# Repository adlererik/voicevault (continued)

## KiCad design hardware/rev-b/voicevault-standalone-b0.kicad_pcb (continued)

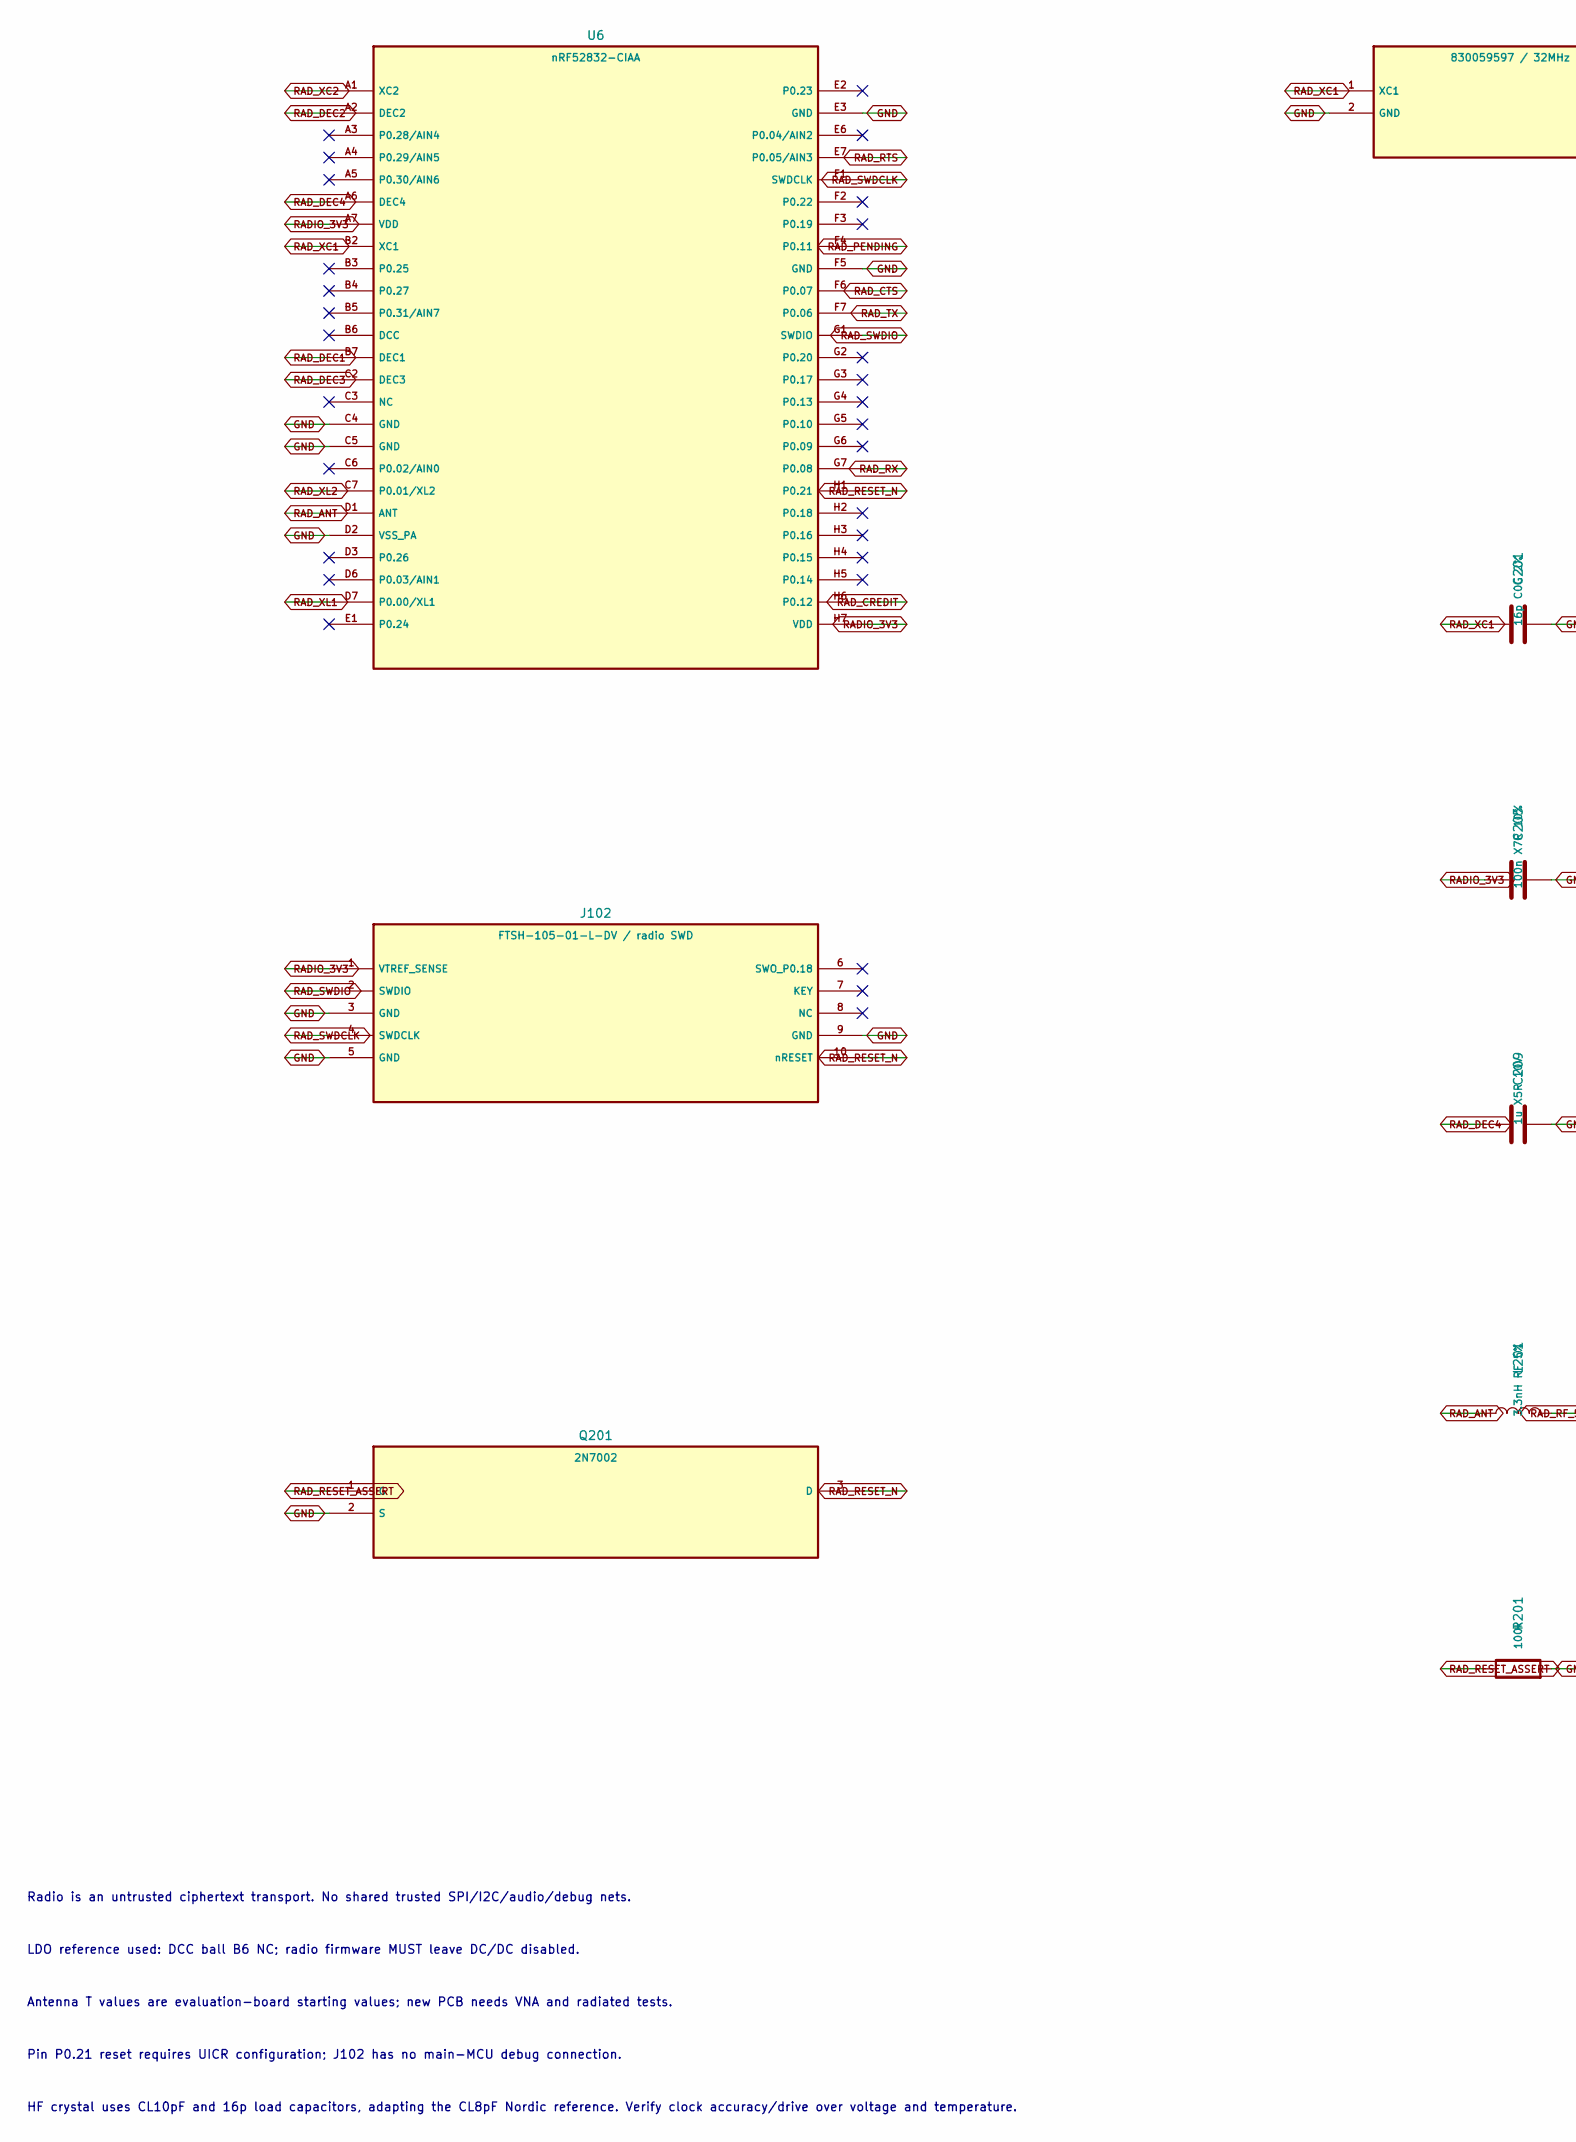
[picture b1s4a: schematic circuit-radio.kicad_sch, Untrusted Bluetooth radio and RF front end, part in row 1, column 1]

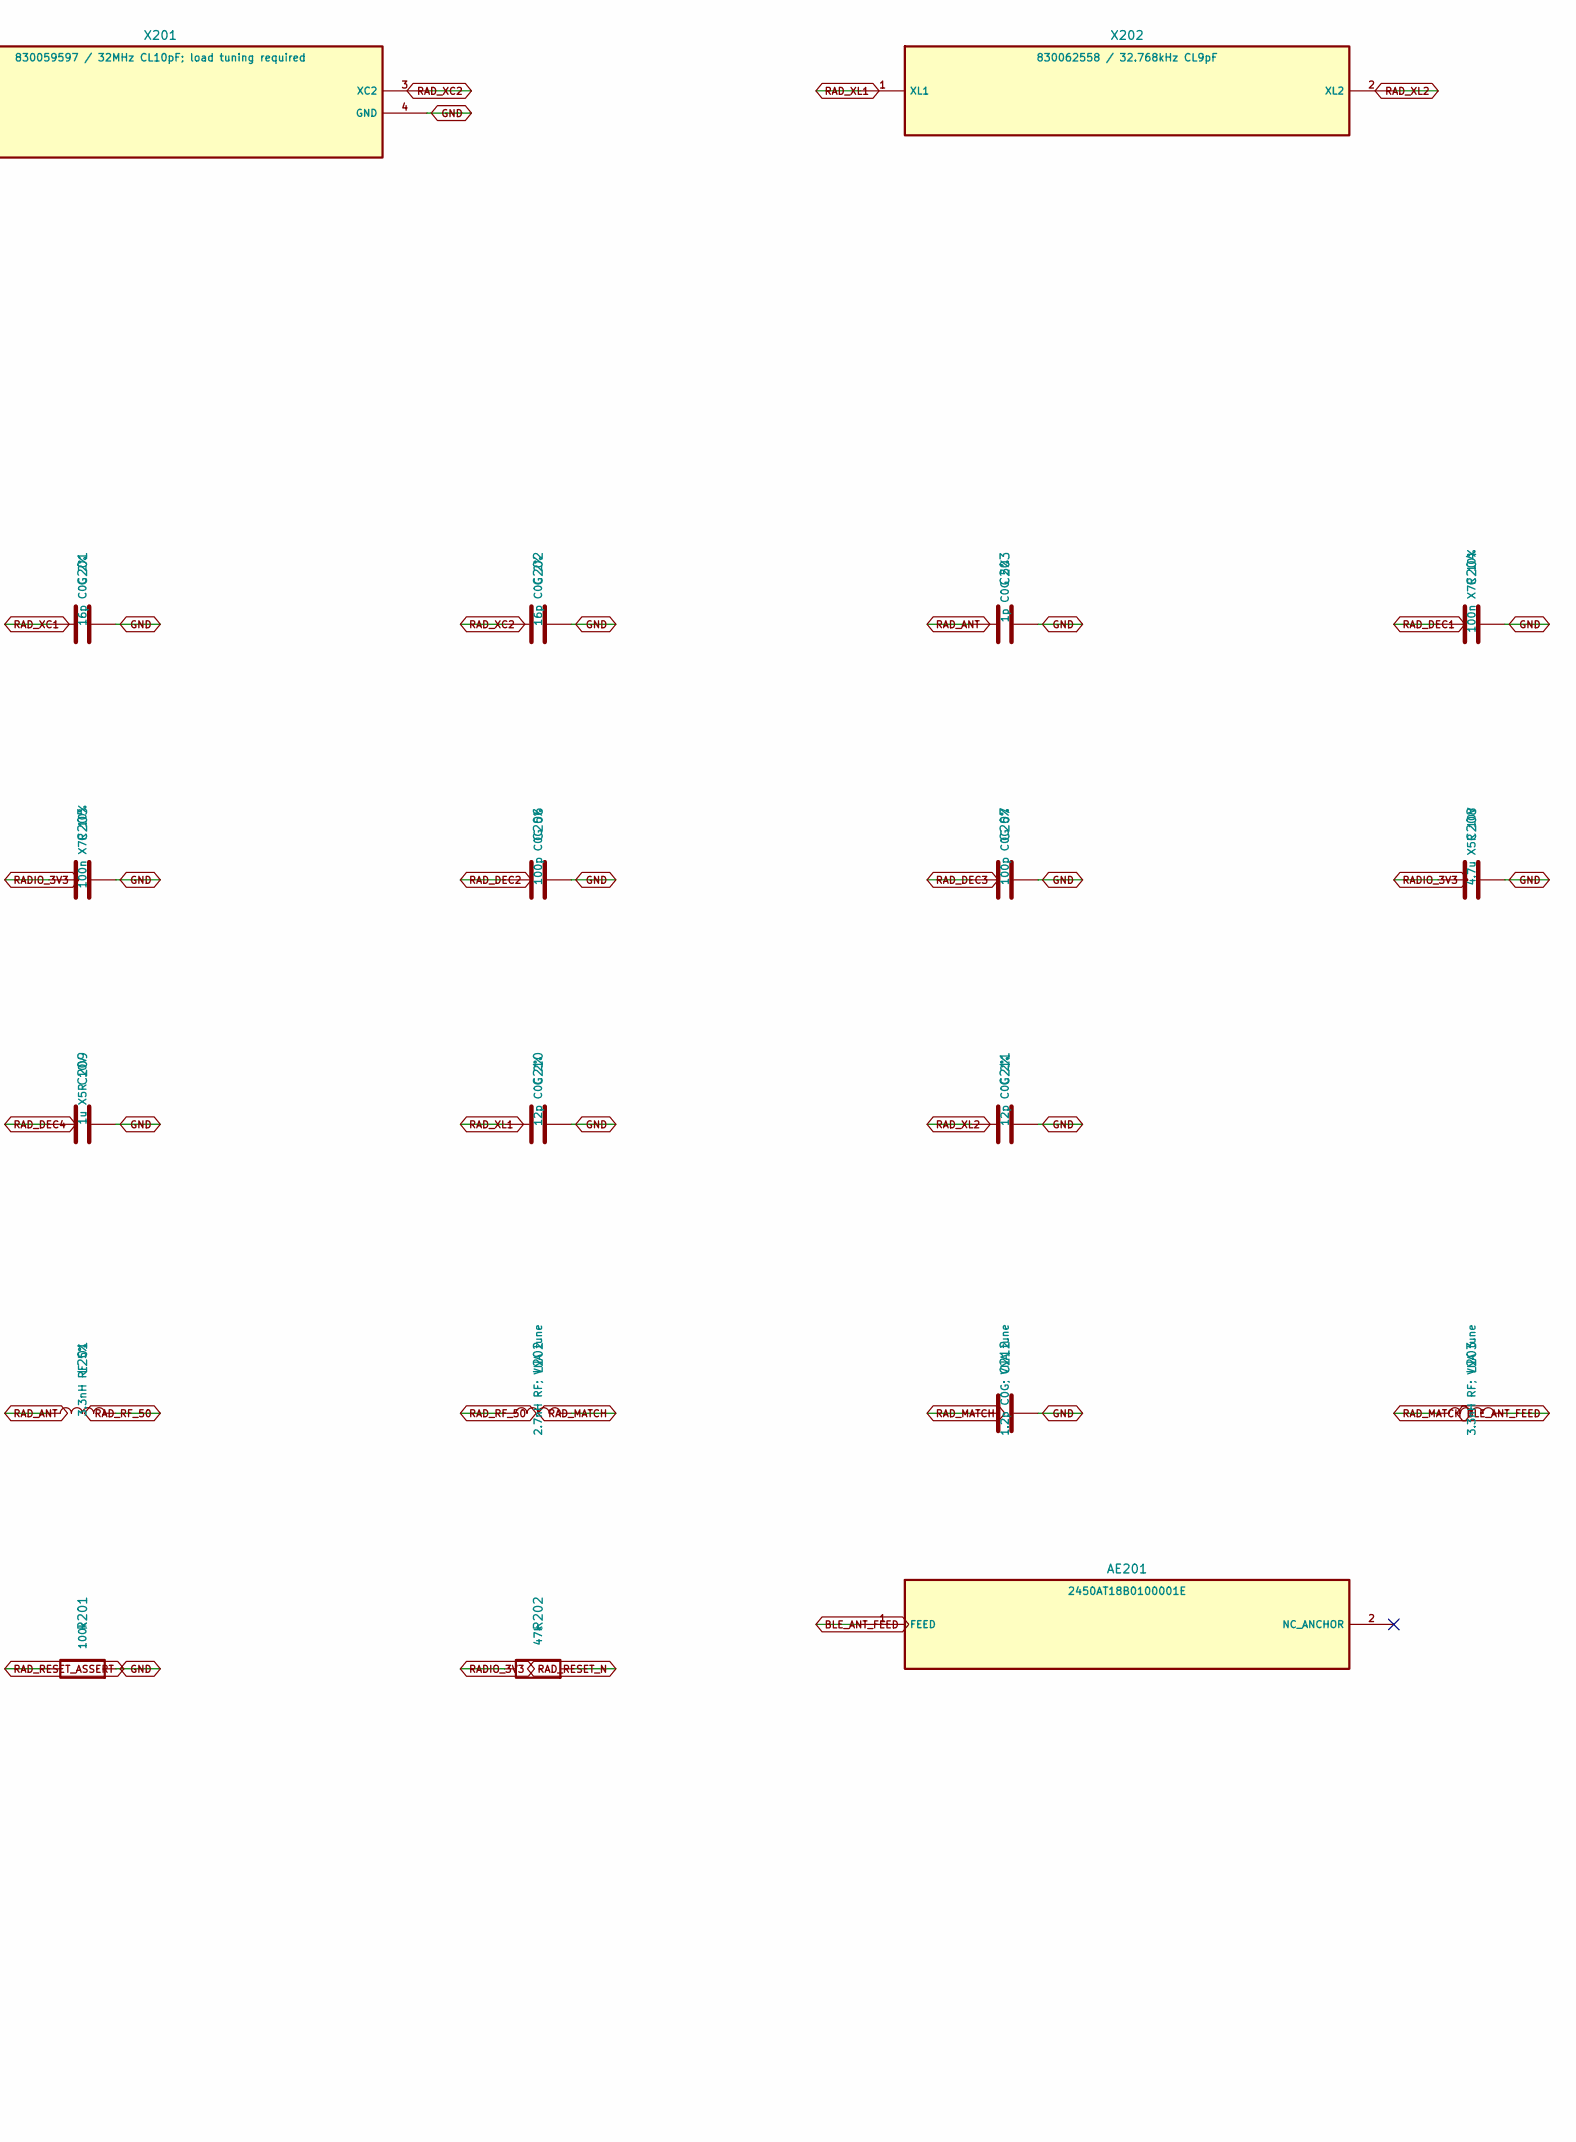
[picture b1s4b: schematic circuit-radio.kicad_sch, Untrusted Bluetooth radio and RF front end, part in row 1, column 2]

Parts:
AE201: 2450AT18B0100001E; Johanson_2450AT18x100
C201, C202: 16p C0G 2%; C_0201_0603Metric
C203: 1p C0G 5%; C_0201_0603Metric
C204, C205: 100n X7R 10%; C_0201_0603Metric
C206, C207: 100p C0G 5%; C_0201_0603Metric
C208: 4.7u X5R 10V; C_0603_1608Metric
C209: 1u X5R 10V; C_0402_1005Metric
C210, C211: 12p C0G 2%; C_0201_0603Metric
C212: 1.2p C0G; VNA tune; C_0402_1005Metric
J102: FTSH-105-01-L-DV / radio SWD; Samtec_FTSH-105-01-L-DV
L201: 3.3nH RF 5%; L_0201_0603Metric
L202: 2.7nH RF; VNA tune; L_0402_1005Metric
L203: 3.3nH RF; VNA tune; L_0402_1005Metric
Q201: 2N7002; SOT-23
R201: 100k; R_0402_1005Metric
R202: 47k; R_0402_1005Metric
U6: nRF52832-CIAA; nRF52832_CIAA_Nordic
X201: 830059597 / 32MHz CL10pF; load tuning required; Crystal_SMD_2016-4Pin_2.0x1.6mm
X202: 830062558 / 32.768kHz CL9pF; Crystal_SMD_2012-2Pin_2.0x1.2mm

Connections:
BLE_ANT_FEED: AE201.1 (FEED), L203.2
GND: C201.2, C202.2, C203.2, C204.2, C205.2, C206.2, C207.2, C208.2, C209.2, C210.2, C211.2, C212.2, J102.3 (GND), J102.5 (GND), J102.9 (GND), Q201.2 (S), R201.2, U6.C4 (GND), U6.C5 (GND), U6.D2 (VSS_PA), U6.E3 (GND), U6.F5 (GND), X201.2 (GND), X201.4 (GND); also elsewhere on the board
RADIO_3V3: C205.1, C208.1, J102.1 (VTREF_SENSE), R202.1, U6.A7 (VDD), U6.H7 (VDD); also elsewhere on the board
RAD_ANT: C203.1, L201.1, U6.D1 (ANT)
RAD_CREDIT: U6.H6 (P0.12); also elsewhere on the board
RAD_CTS: U6.F6 (P0.07); also elsewhere on the board
RAD_DEC1: C204.1, U6.B7 (DEC1)
RAD_DEC2: C206.1, U6.A2 (DEC2)
RAD_DEC3: C207.1, U6.C2 (DEC3)
RAD_DEC4: C209.1, U6.A6 (DEC4)
RAD_MATCH: C212.1, L202.2, L203.1
RAD_PENDING: U6.F4 (P0.11); also elsewhere on the board
RAD_RESET_ASSERT: Q201.1 (G), R201.1; also elsewhere on the board
RAD_RESET_N: J102.10 (nRESET), Q201.3 (D), R202.2, U6.H1 (P0.21)
RAD_RF_50: L201.2, L202.1
RAD_RTS: U6.E7 (P0.05/AIN3); also elsewhere on the board
RAD_RX: U6.G7 (P0.08); also elsewhere on the board
RAD_SWDCLK: J102.4 (SWDCLK), U6.F1 (SWDCLK)
RAD_SWDIO: J102.2 (SWDIO), U6.G1 (SWDIO)
RAD_TX: U6.F7 (P0.06); also elsewhere on the board
RAD_XC1: C201.1, U6.B2 (XC1), X201.1 (XC1)
RAD_XC2: C202.1, U6.A1 (XC2), X201.3 (XC2)
RAD_XL1: C210.1, U6.D7 (P0.00/XL1), X202.1 (XL1)
RAD_XL2: C211.1, U6.C7 (P0.01/XL2), X202.2 (XL2)

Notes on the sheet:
Radio is an untrusted ciphertext transport. No shared trusted SPI/I2C/audio/debug nets.
LDO reference used: DCC ball B6 NC; radio firmware MUST leave DC/DC disabled.
Antenna T values are evaluation-board starting values; new PCB needs VNA and radiated tests.
Pin P0.21 reset requires UICR configuration; J102 has no main-MCU debug connection.
HF crystal uses CL10pF and 16p load capacitors, adapting the CL8pF Nordic reference. Verify clock accuracy/drive over voltage and temperature.

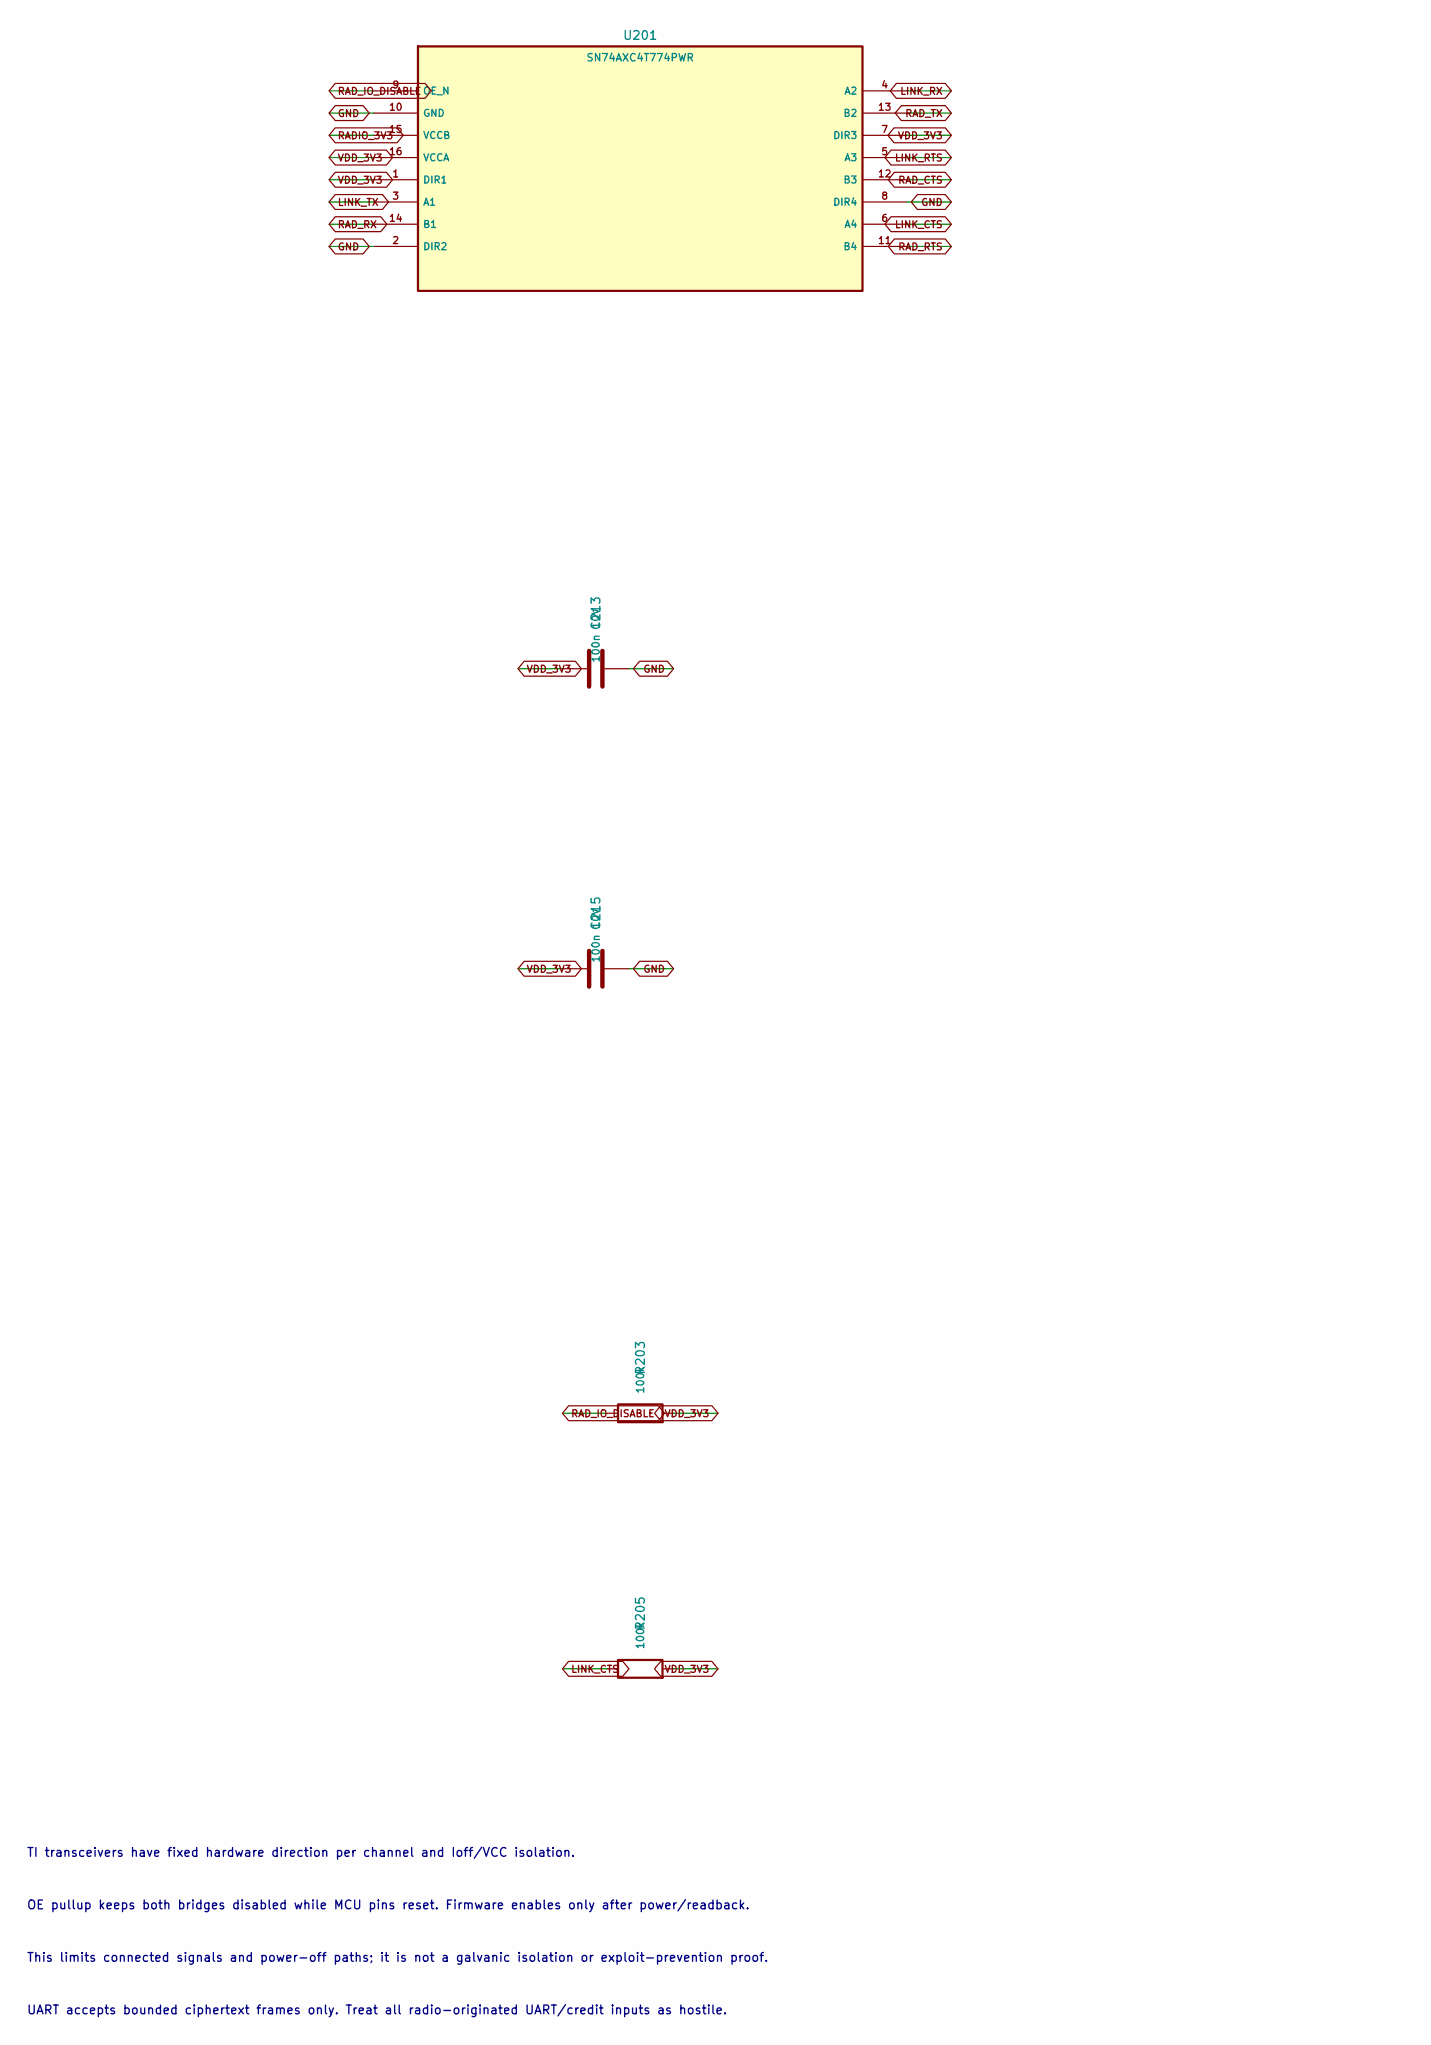
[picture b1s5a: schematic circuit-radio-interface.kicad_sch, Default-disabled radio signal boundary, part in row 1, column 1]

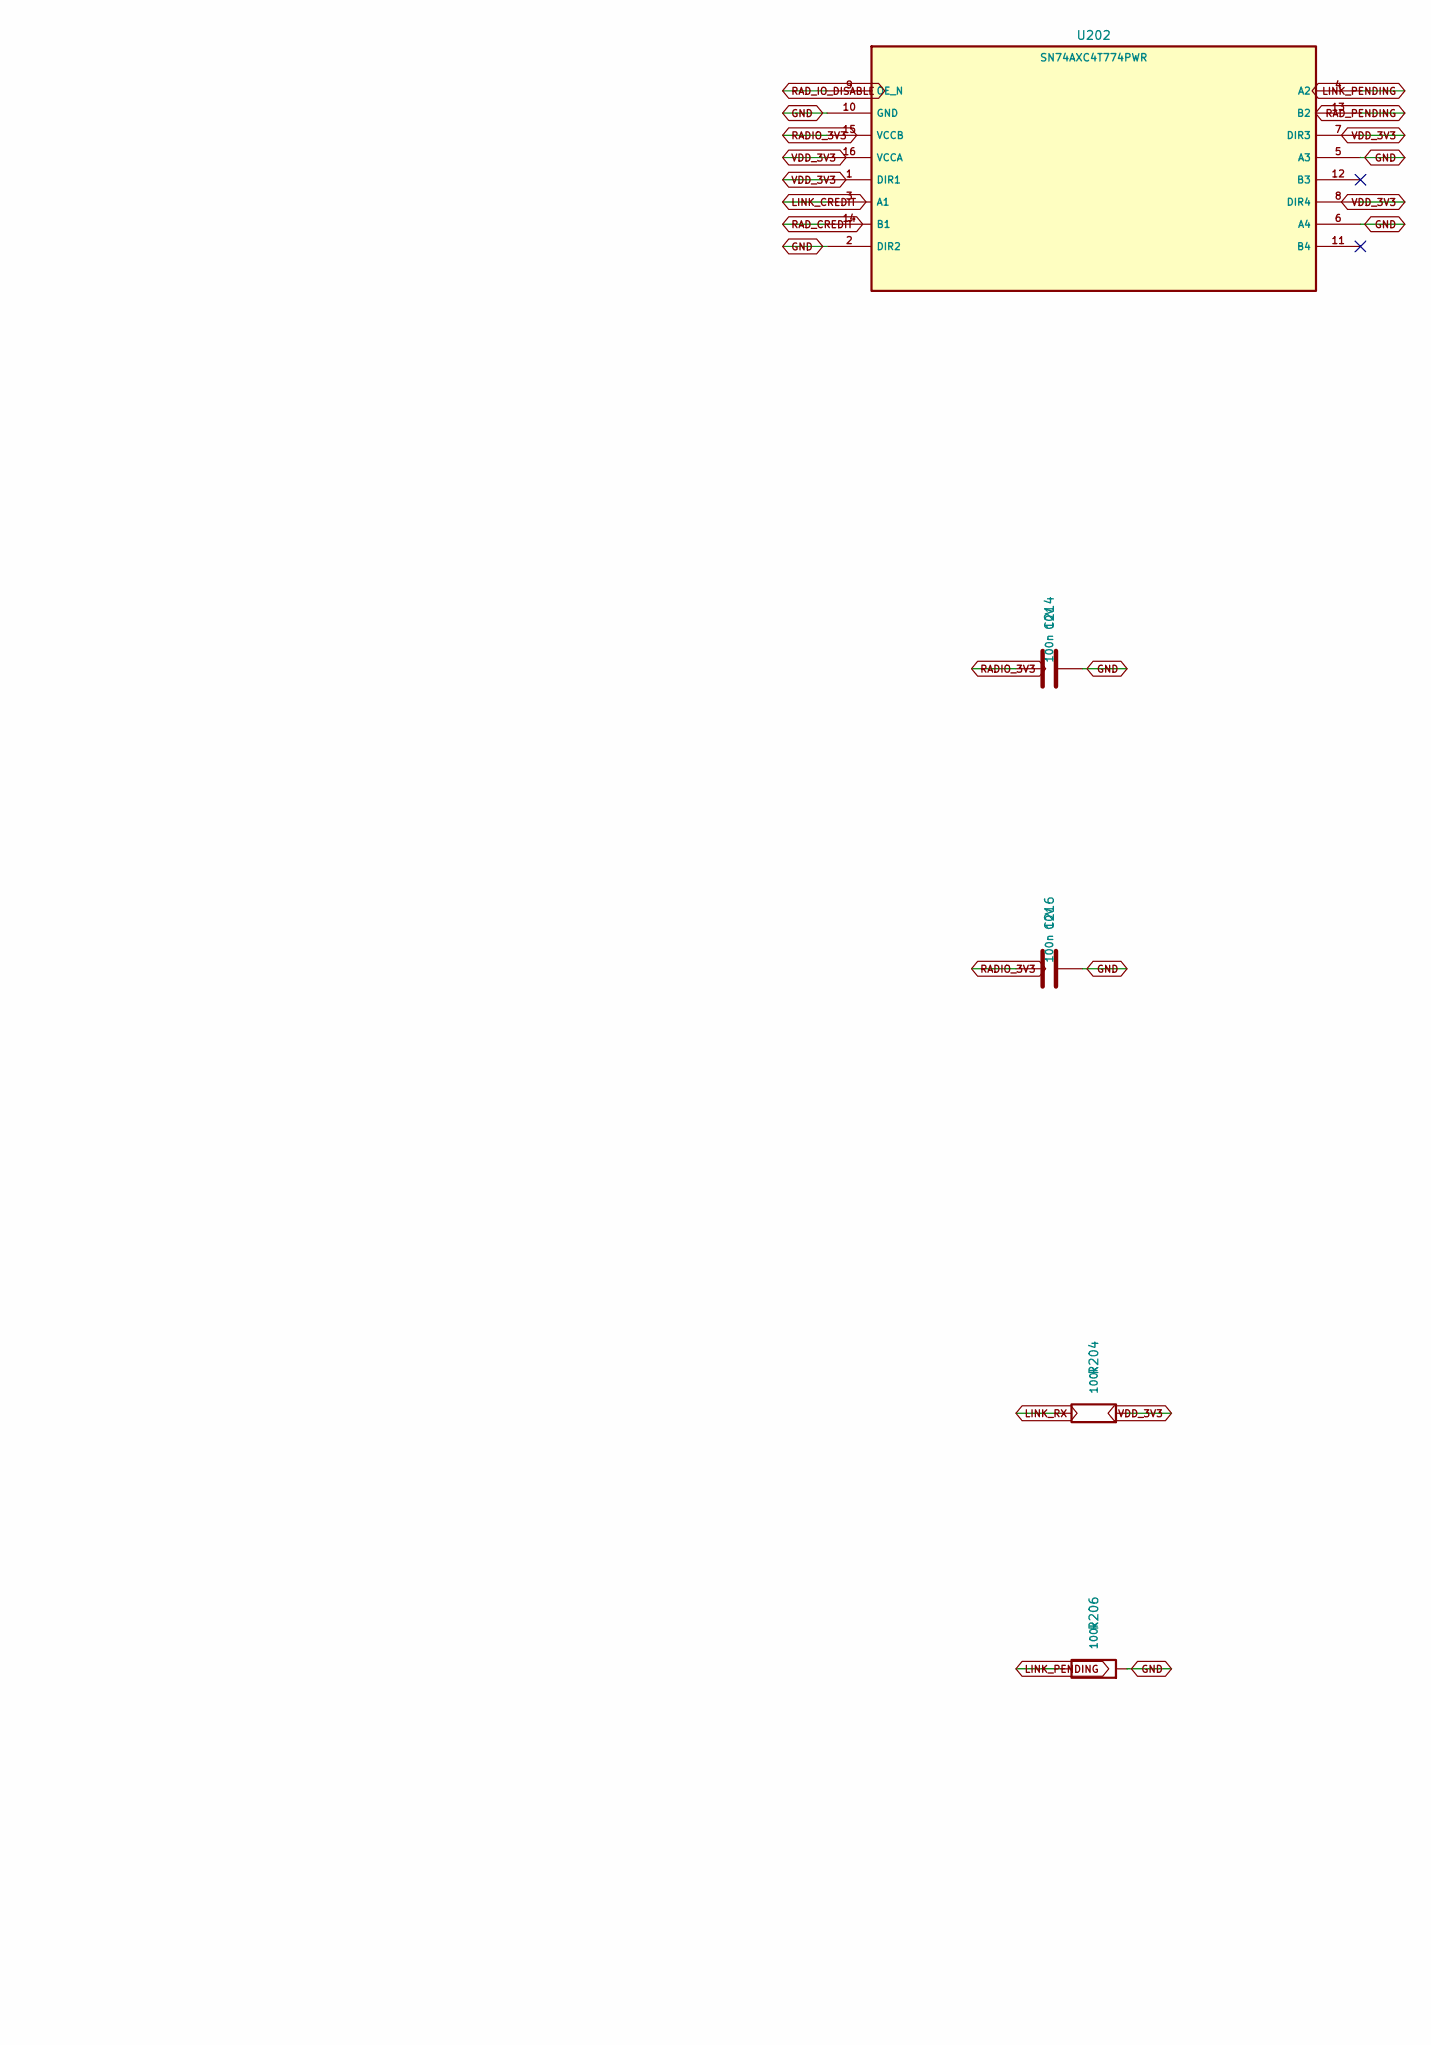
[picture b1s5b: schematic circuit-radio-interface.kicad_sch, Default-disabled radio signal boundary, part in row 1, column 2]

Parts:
C213, C214, C215, C216: 100n 10V; C_0402_1005Metric
R203, R204, R205, R206: 100k; R_0402_1005Metric
U201, U202: SN74AXC4T774PWR; TSSOP-16_4.4x5mm_P0.65mm

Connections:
GND: C213.2, C214.2, C215.2, C216.2, R206.2, U201.2 (DIR2), U201.8 (DIR4), U201.10 (GND), U202.2 (DIR2), U202.5 (A3), U202.6 (A4), U202.10 (GND); also elsewhere on the board
LINK_CREDIT: U202.3 (A1); also elsewhere on the board
LINK_CTS: R205.1, U201.6 (A4); also elsewhere on the board
LINK_PENDING: R206.1, U202.4 (A2); also elsewhere on the board
LINK_RTS: U201.5 (A3); also elsewhere on the board
LINK_RX: R204.1, U201.4 (A2); also elsewhere on the board
LINK_TX: U201.3 (A1); also elsewhere on the board
RADIO_3V3: C214.1, C216.1, U201.15 (VCCB), U202.15 (VCCB); also elsewhere on the board
RAD_CREDIT: U202.14 (B1); also elsewhere on the board
RAD_CTS: U201.12 (B3); also elsewhere on the board
RAD_IO_DISABLE: R203.1, U201.9 (OE_N), U202.9 (OE_N); also elsewhere on the board
RAD_PENDING: U202.13 (B2); also elsewhere on the board
RAD_RTS: U201.11 (B4); also elsewhere on the board
RAD_RX: U201.14 (B1); also elsewhere on the board
RAD_TX: U201.13 (B2); also elsewhere on the board
VDD_3V3: C213.1, C215.1, R203.2, R204.2, R205.2, U201.1 (DIR1), U201.7 (DIR3), U201.16 (VCCA), U202.1 (DIR1), U202.7 (DIR3), U202.8 (DIR4), U202.16 (VCCA); also elsewhere on the board

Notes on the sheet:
TI transceivers have fixed hardware direction per channel and Ioff/VCC isolation.
OE pullup keeps both bridges disabled while MCU pins reset. Firmware enables only after power/readback.
This limits connected signals and power-off paths; it is not a galvanic isolation or exploit-prevention proof.
UART accepts bounded ciphertext frames only. Treat all radio-originated UART/credit inputs as hostile.

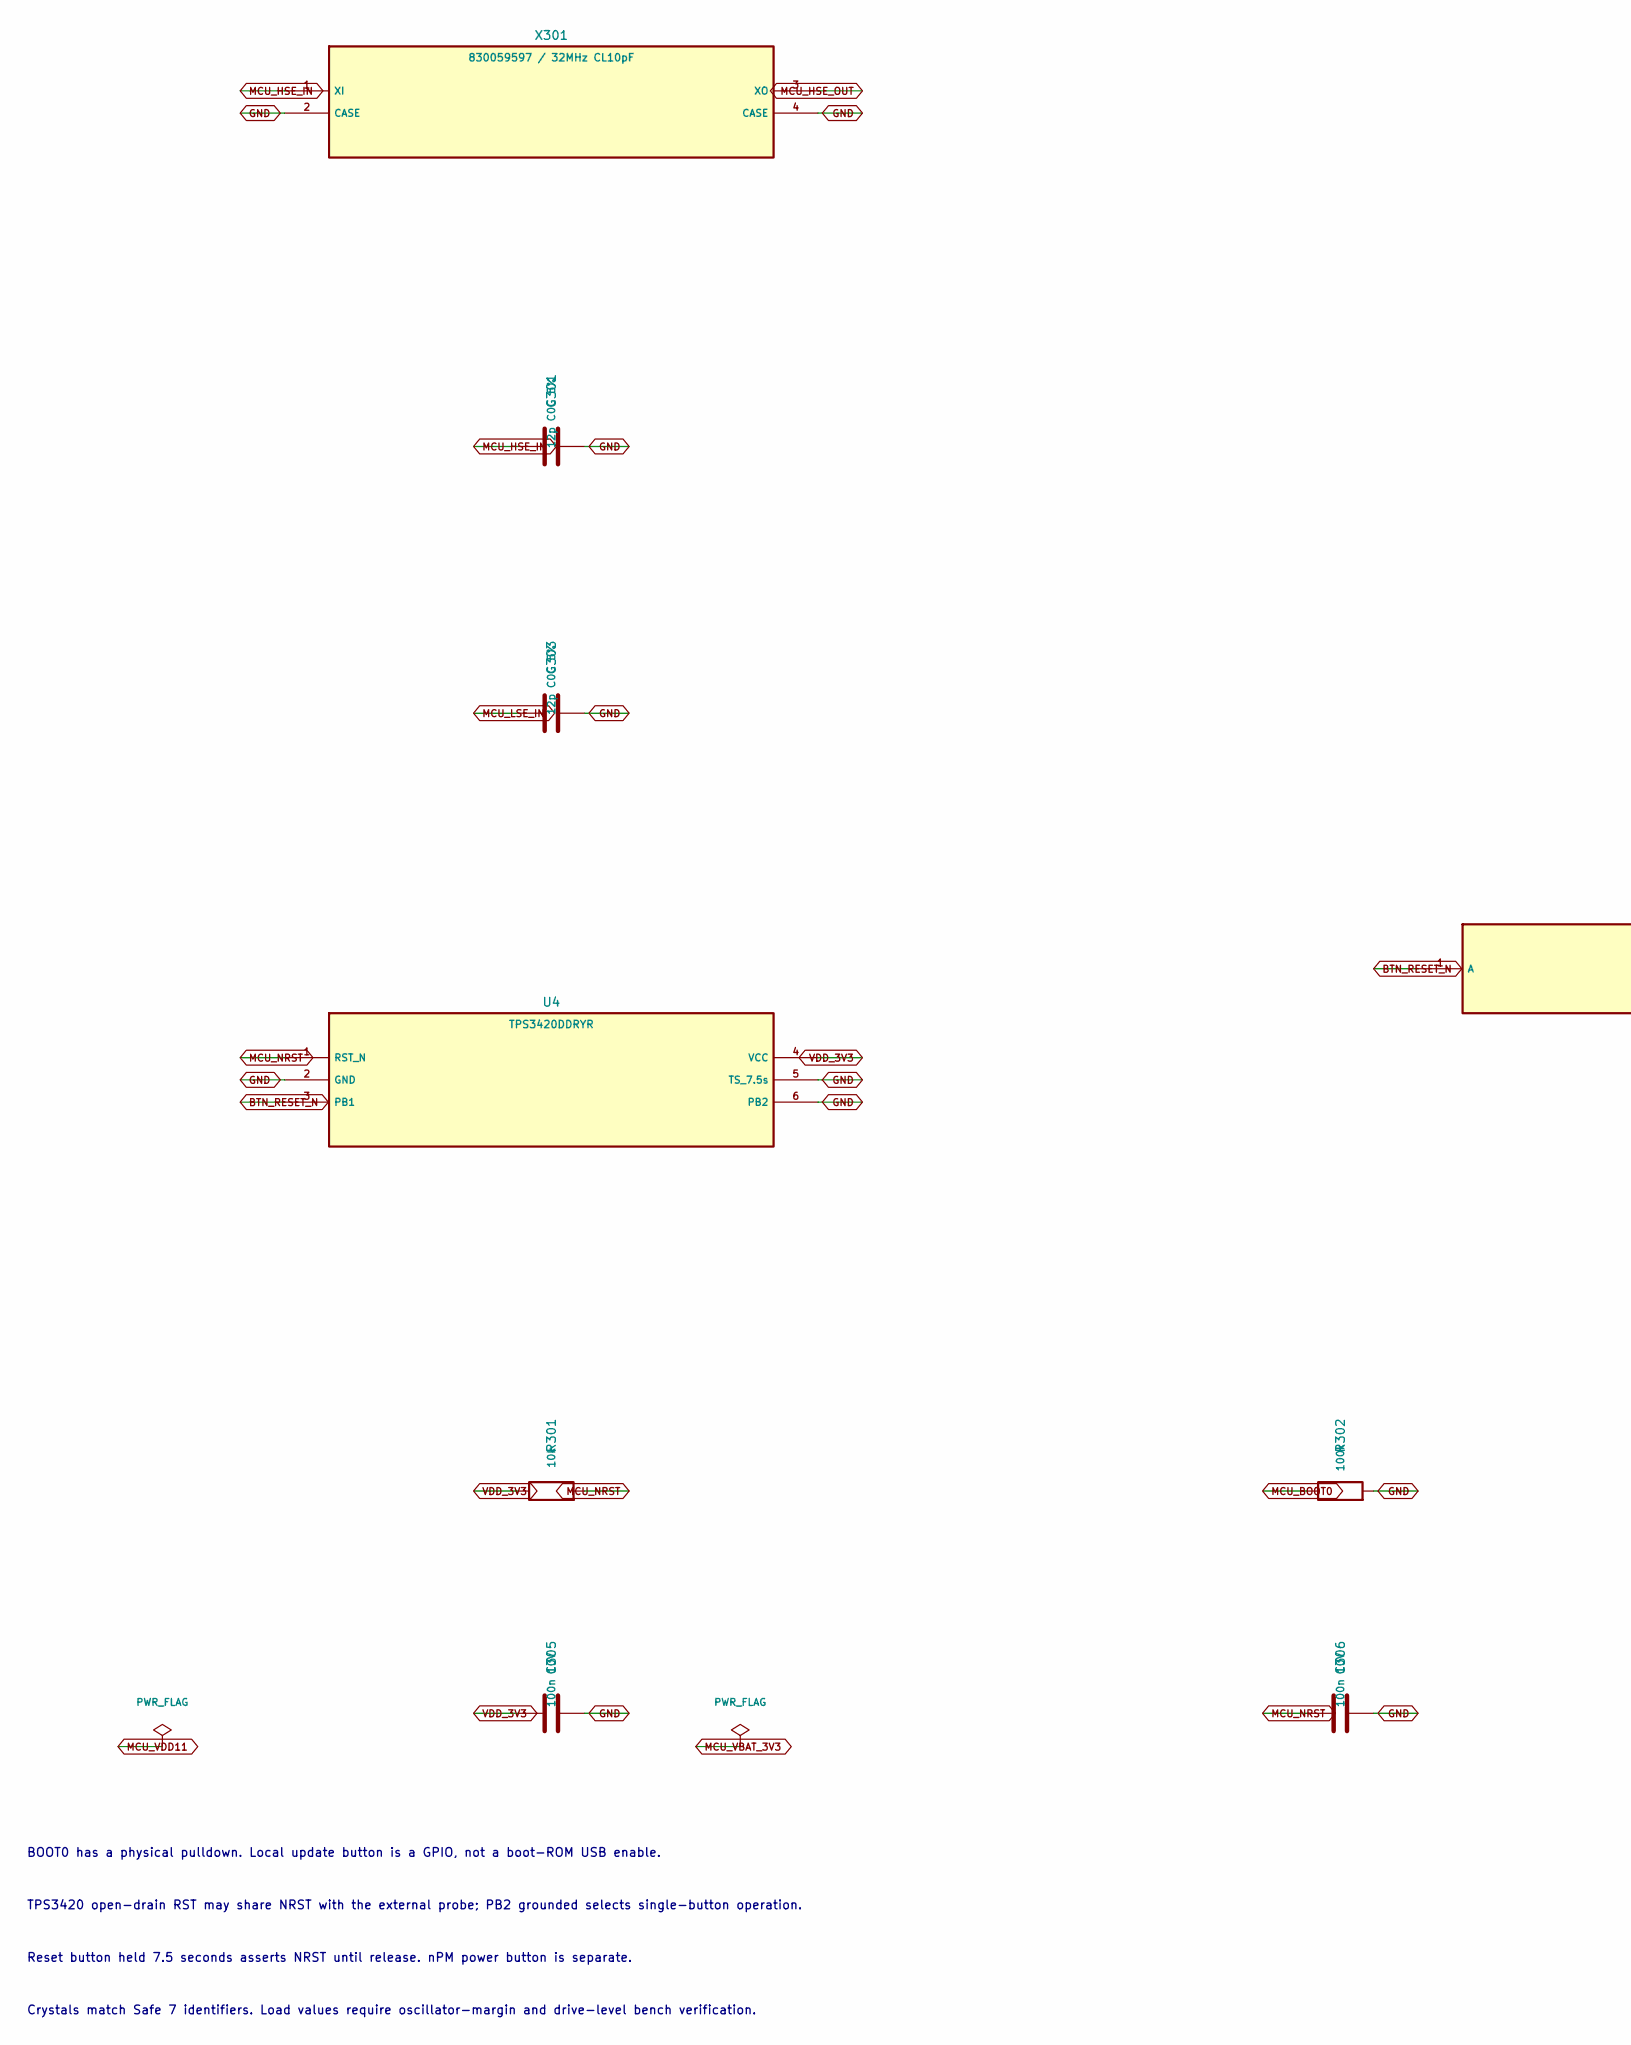
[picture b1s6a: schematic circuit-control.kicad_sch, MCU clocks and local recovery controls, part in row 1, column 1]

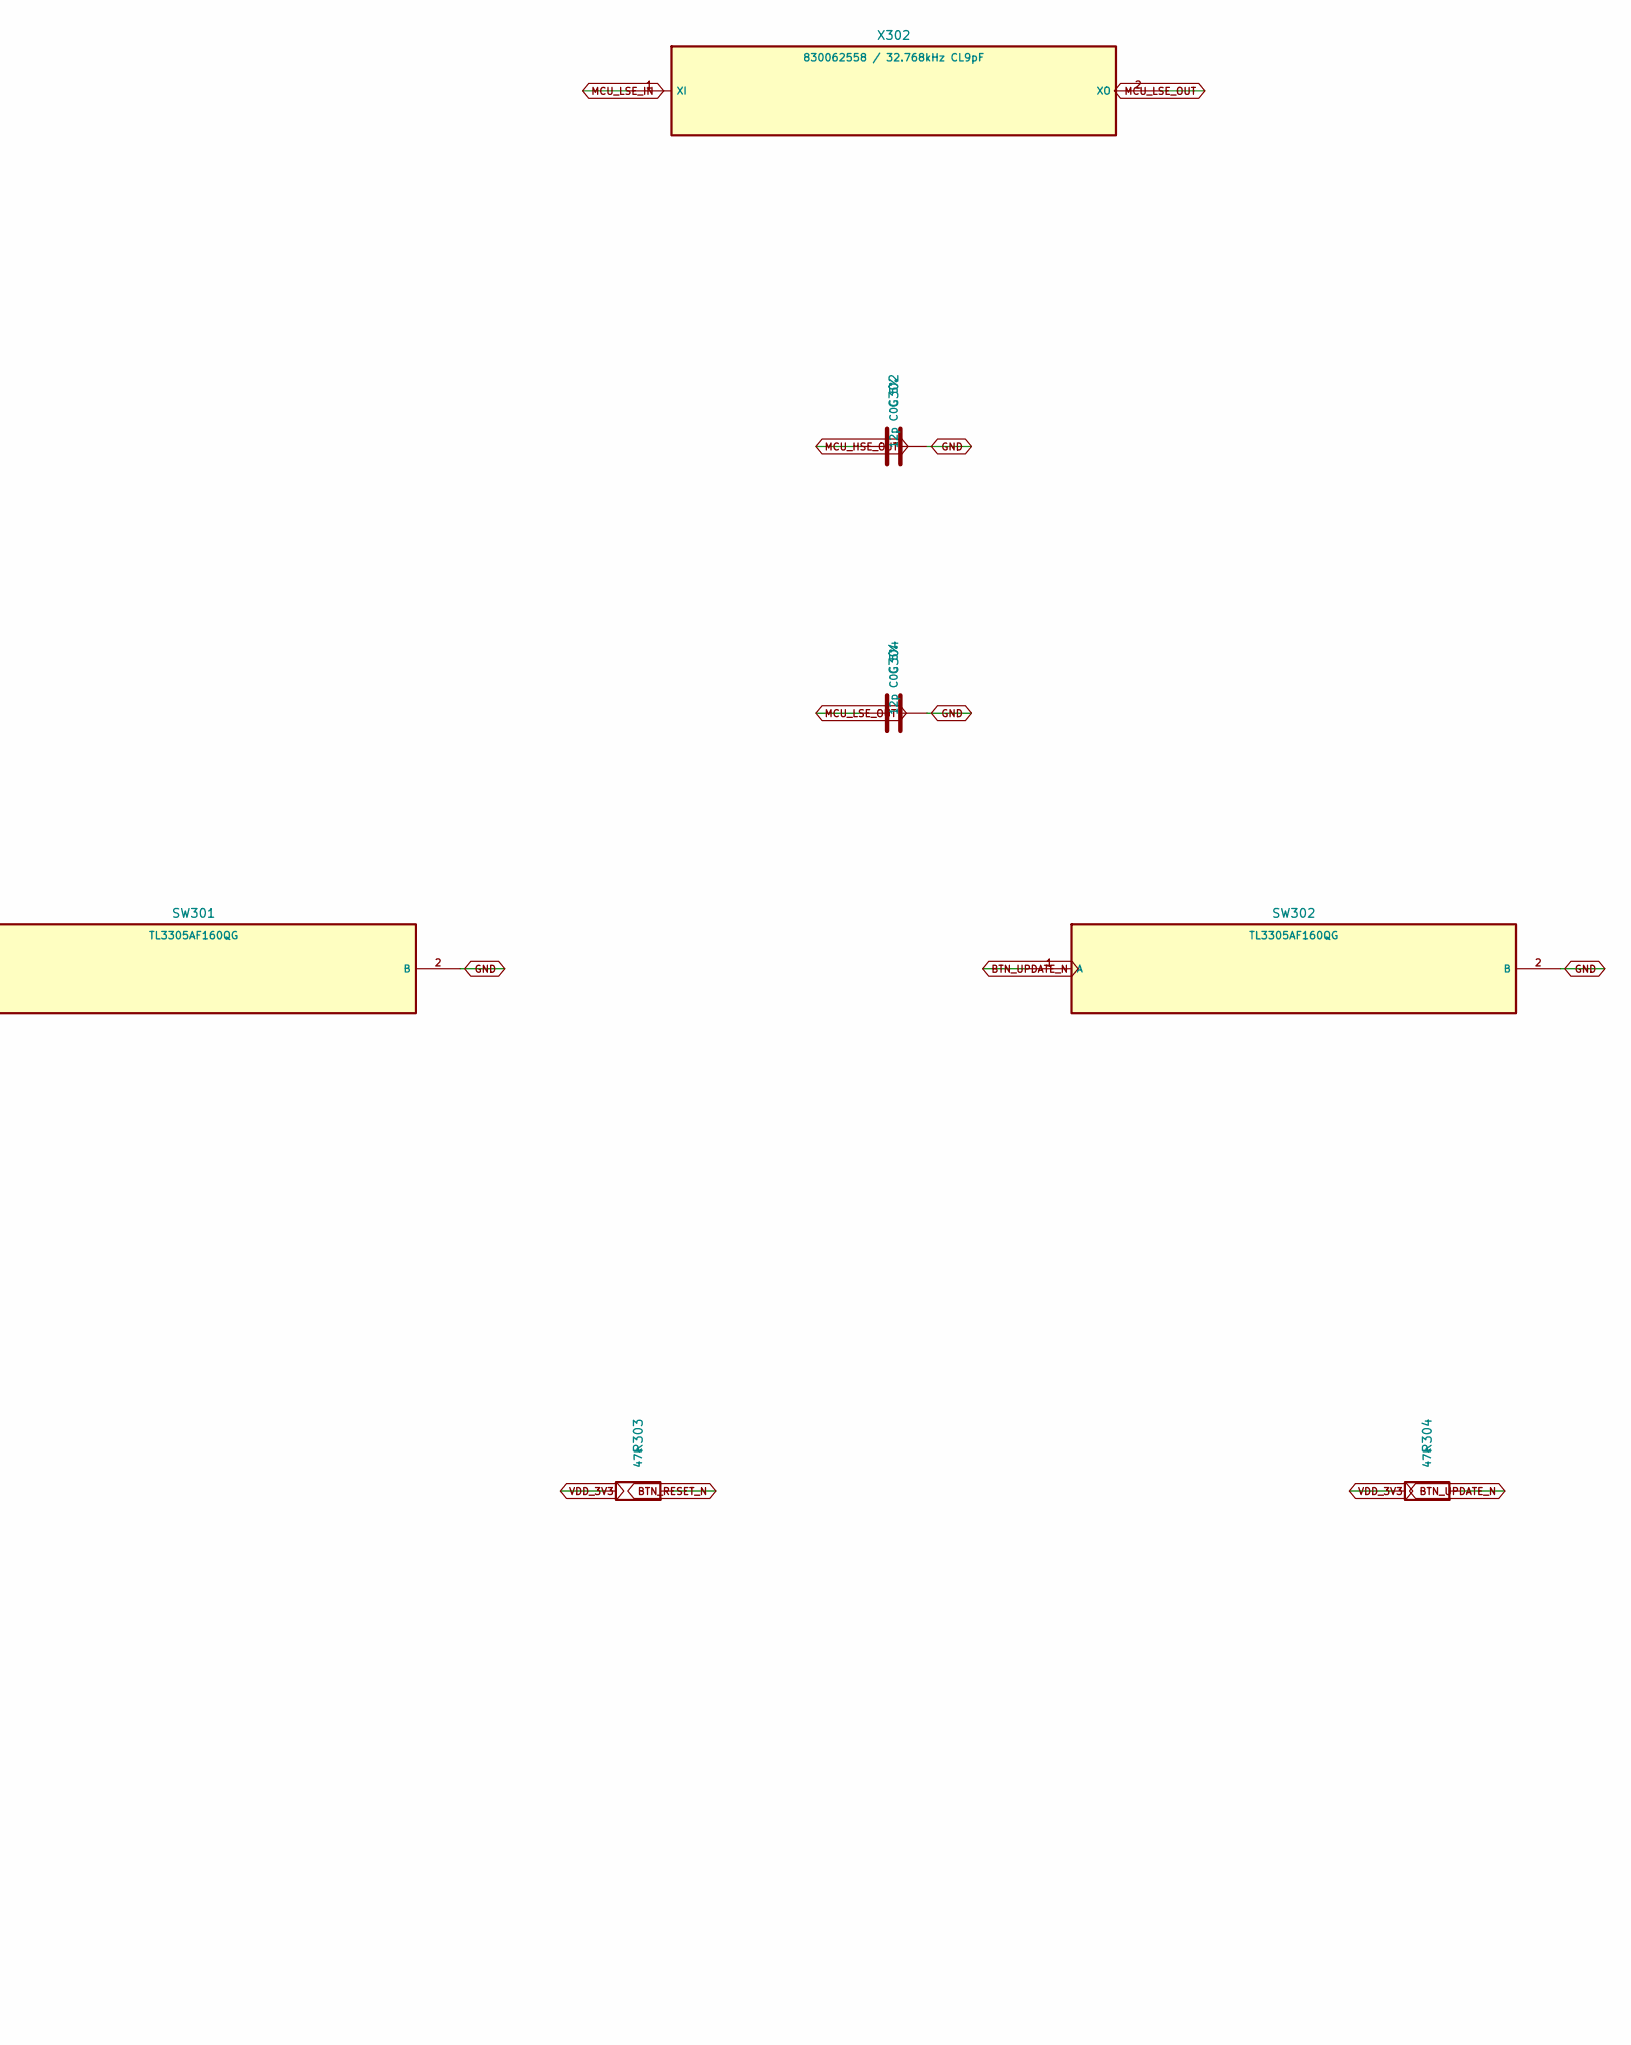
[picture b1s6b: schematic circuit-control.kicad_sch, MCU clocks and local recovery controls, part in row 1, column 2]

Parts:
C301, C302, C303, C304: 12p C0G 5%; C_0402_1005Metric
C305, C306: 100n 10V; C_0402_1005Metric
R301: 10k; R_0402_1005Metric
R302: 100k; R_0402_1005Metric
R303, R304: 47k; R_0402_1005Metric
SW301, SW302: TL3305AF160QG; SW_SPST_TL3305A
U4: TPS3420DDRYR; Texas_USON-6_1x1.45mm_P0.5mm_SMD
X301: 830059597 / 32MHz CL10pF; Crystal_SMD_2016-4Pin_2.0x1.6mm
X302: 830062558 / 32.768kHz CL9pF; Crystal_SMD_2012-2Pin_2.0x1.2mm

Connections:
BTN_RESET_N: R303.2, SW301.1 (A), U4.3 (PB1); also elsewhere on the board
BTN_UPDATE_N: R304.2, SW302.1 (A); also elsewhere on the board
GND: C301.2, C302.2, C303.2, C304.2, C305.2, C306.2, R302.2, SW301.2 (B), SW302.2 (B), U4.2 (GND), U4.5 (TS_7.5s), U4.6 (PB2), X301.2 (CASE), X301.4 (CASE); also elsewhere on the board
MCU_BOOT0: R302.1; also elsewhere on the board
MCU_HSE_IN: C301.1, X301.1 (XI); also elsewhere on the board
MCU_HSE_OUT: C302.1, X301.3 (XO); also elsewhere on the board
MCU_LSE_IN: C303.1, X302.1 (XI); also elsewhere on the board
MCU_LSE_OUT: C304.1, X302.2 (XO); also elsewhere on the board
MCU_NRST: C306.1, R301.2, U4.1 (RST_N); also elsewhere on the board
VDD_3V3: C305.1, R301.1, R303.1, R304.1, U4.4 (VCC); also elsewhere on the board

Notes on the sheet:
BOOT0 has a physical pulldown. Local update button is a GPIO, not a boot-ROM USB enable.
TPS3420 open-drain RST may share NRST with the external probe; PB2 grounded selects single-button operation.
Reset button held 7.5 seconds asserts NRST until release. nPM power button is separate.
Crystals match Safe 7 identifiers. Load values require oscillator-margin and drive-level bench verification.
